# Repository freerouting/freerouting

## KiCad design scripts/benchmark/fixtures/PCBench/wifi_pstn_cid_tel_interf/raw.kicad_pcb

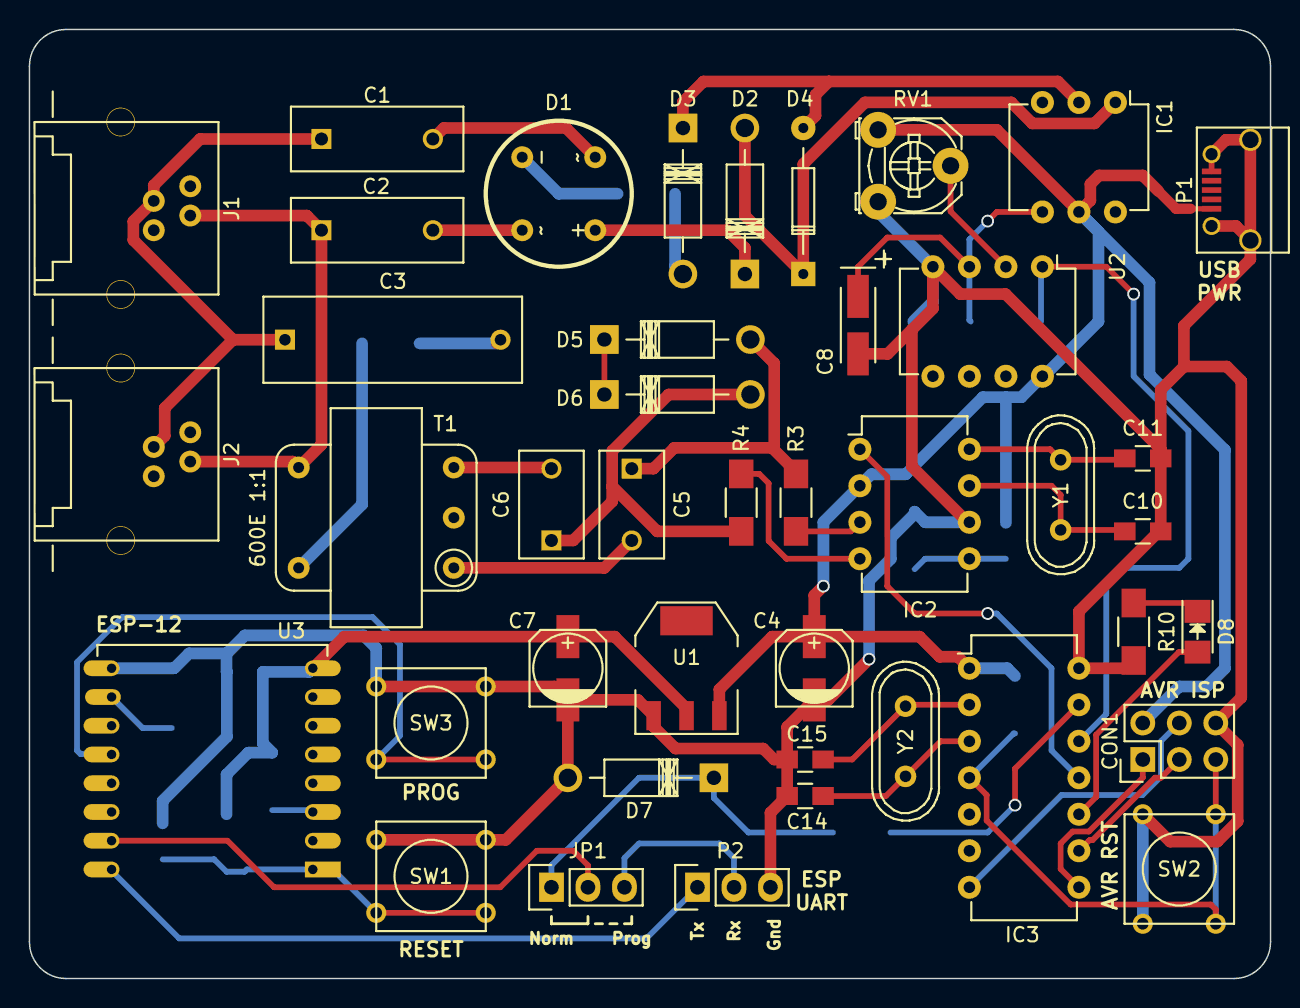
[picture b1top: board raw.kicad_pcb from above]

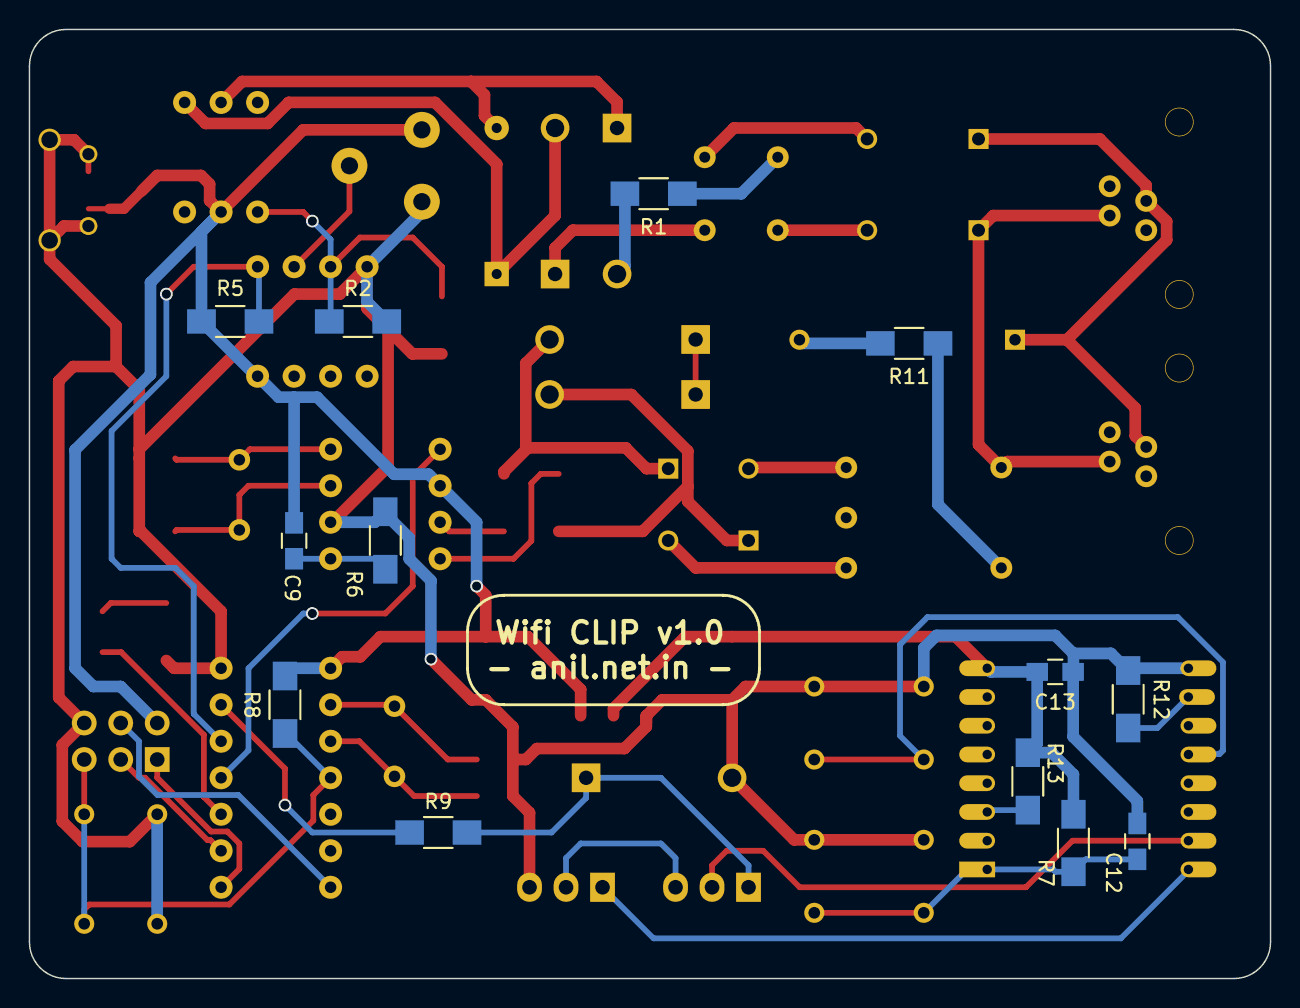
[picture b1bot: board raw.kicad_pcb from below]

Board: 2 copper layers, 86.4 x 66.0 mm, 55 parts (13 on the bottom side), 45 nets.

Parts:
C1: 33nF, 150V; C_Disc_D12_P7.75
C2: 33nF, 150v; C_Disc_D12_P7.75
C3: 100nF, 250V; C_Rect_L18_W6_P15
C4, C7: 10uF; c_elec_5x5.3
C5, C6: 47nF; C_Disc_D7.5_P5
C8: 1uF; TantalC_SizeA_EIA-3216_HandSoldering
C9, C12, C13: 0.1uF; C_0805_HandSoldering
C10, C11, C14, C15: 22pF; C_0805_HandSoldering
CON1: AVR-ISP-6; Pin_Header_Straight_2x03
D1: W10M; WOM_BRIDGE
D2, D3: ZENER 8.2V; Diode_DO-41_SOD81_Horizontal_RM10
D4: 1N4148; Diode_DO-35_SOD27_Horizontal_RM10
D5, D6: ZENER 3.3V; Diode_DO-41_SOD81_Horizontal_RM10
D7: 3.3v; Diode_DO-41_SOD81_Horizontal_RM10
D8: LED; LED-1206
IC1: 4N35; DIP-6_W7.62mm
IC2: HT9032D; DIP-8_W7.62mm
IC3: ATTINY84-P; DIP-14_W7.62mm
J1, J2: RJ11_PTH_STAGGER; RJ11_PTH_6P4C_STAG
JP1: RX sel.; Pin_Header_Straight_1x03
P1: USB_OTG; USB_Micro-B
P2: ESP_UART; Pin_Header_Straight_1x03
R1, R6: 100K; R_1206_HandSoldering
R2, R3, R4: 220K; R_1206_HandSoldering
R5: 10K; R_1206_HandSoldering
R7, R8: 4.7K; R_1206_HandSoldering
R9: 1k; R_1206_HandSoldering
R10, R11, R12, R13: 1K; R_1206_HandSoldering
RV1: 10K; Potentiometer_Triwood_RM-065
SW1: ESP_REST; SW_PUSH_SMALL
SW2: AVR_REST; SW_PUSH_SMALL
SW3: PROG; SW_PUSH_SMALL
T1: 600E 1:1; TRANSFO-AUDIO-EL14
U1: LD1117S33TR; SOT-223
U2: LM393; DIP-8_W7.62mm
U3: ESP-12
Y1: 3.579545Mhz; Crystal_HC49-U_Vertical
Y2: 8 Mhz; Crystal_HC49-U_Vertical

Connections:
+3V3: C7.1, C13.2, R7.1, R13.1, U1.2, U3.8
+5V: C4.1, C9.1, CON1.2, IC1.5, IC2.2, IC3.1, P1.1, R5.1, R8.2, RV1.1, U1.3, U2.8
AVR_MISO: CON1.1, IC3.8
AVR_MOSI: CON1.4, IC3.7
AVR_REST: CON1.5, IC3.4, R8.1, SW2.2
AVR_SCL: CON1.3, IC3.9
CLIP: IC2.1, IC3.11
GND: C4.2, C7.2, C8.2, C10.2, C11.2, C12.2, C13.1, C14.2, C15.2, CON1.6, D7.2, IC2.6, IC3.14, P1.5, P1.6, P2.3, R2.2, R6.2, R10.2, R12.1, RV1.3, SW1.1, SW2.1, SW3.1, U1.1, U2.4, U3.9
NUMOUT: IC3.13, R9.1
unnamed: C1.2, D1.4
unnamed: C2.2, D1.2
unnamed: C3.2, R11.2
unnamed: C5.1, D5.2, R3.1
unnamed: C5.2, T1.1
unnamed: C6.1, D6.2, R4.1
unnamed: C6.2, T1.3
unnamed: C8.1, IC1.4, R2.1, U2.3
unnamed: C9.2, IC2.5, R6.1
unnamed: C10.1, IC2.7, Y1.1
unnamed: C11.1, IC2.8, Y1.2
unnamed: C12.1, R7.2, SW1.2, U3.1
unnamed: C14.1, IC3.3, Y2.1
unnamed: C15.1, IC3.2, Y2.2
unnamed: D1.1, D2.1
unnamed: D1.3, R1.1
unnamed: D2.2, D4.1, IC1.1
unnamed: D3.1, D4.2, IC1.2
unnamed: D3.2, R1.2
unnamed: D5.1, D6.1
unnamed: D7.1, JP1.1, R9.2
unnamed: D8.1, R10.1
unnamed: D8.2, IC3.10
unnamed: IC2.3, R3.2
unnamed: IC2.4, R4.2
unnamed: JP1.2, U3.15
unnamed: JP1.3, P2.2
unnamed: P2.1, U3.16
unnamed: R11.1, T1.5
unnamed: R12.2, U3.10
unnamed: R13.2, U3.3
unnamed: RV1.2, U2.2
unnamed: SW3.2, U3.12
RING: IC3.12, R5.2, U2.1
TEL1: C1.1, C3.1, J1.2, J2.2
TEL2: C2.1, J1.3, J2.3, T1.4

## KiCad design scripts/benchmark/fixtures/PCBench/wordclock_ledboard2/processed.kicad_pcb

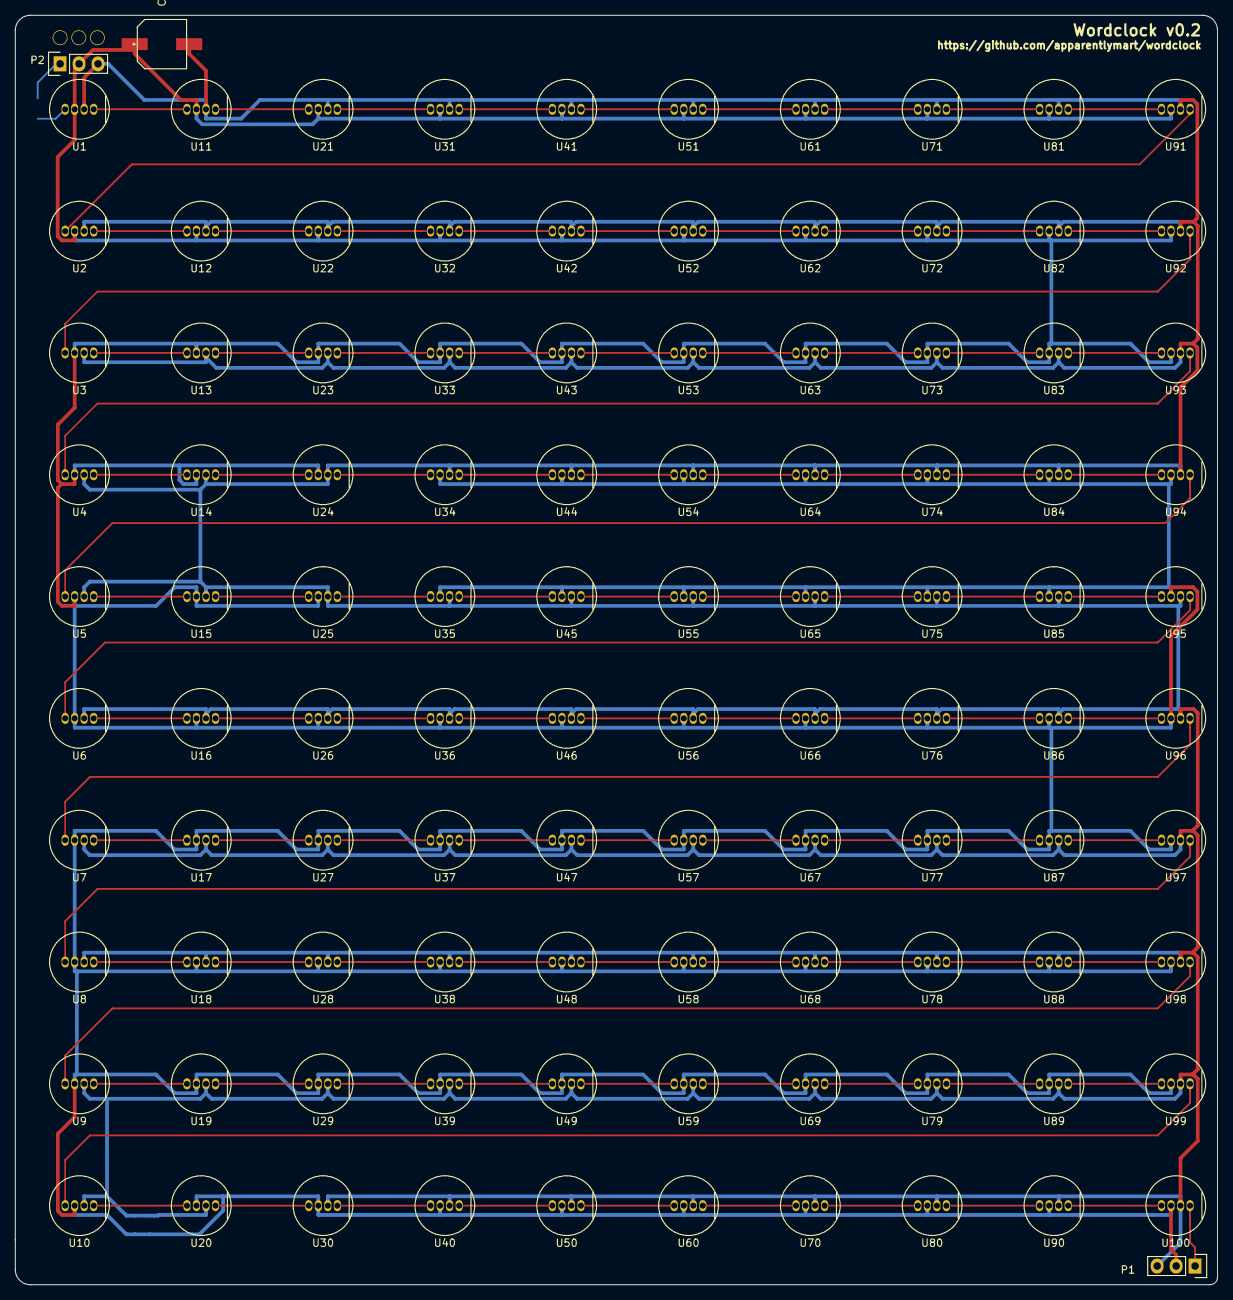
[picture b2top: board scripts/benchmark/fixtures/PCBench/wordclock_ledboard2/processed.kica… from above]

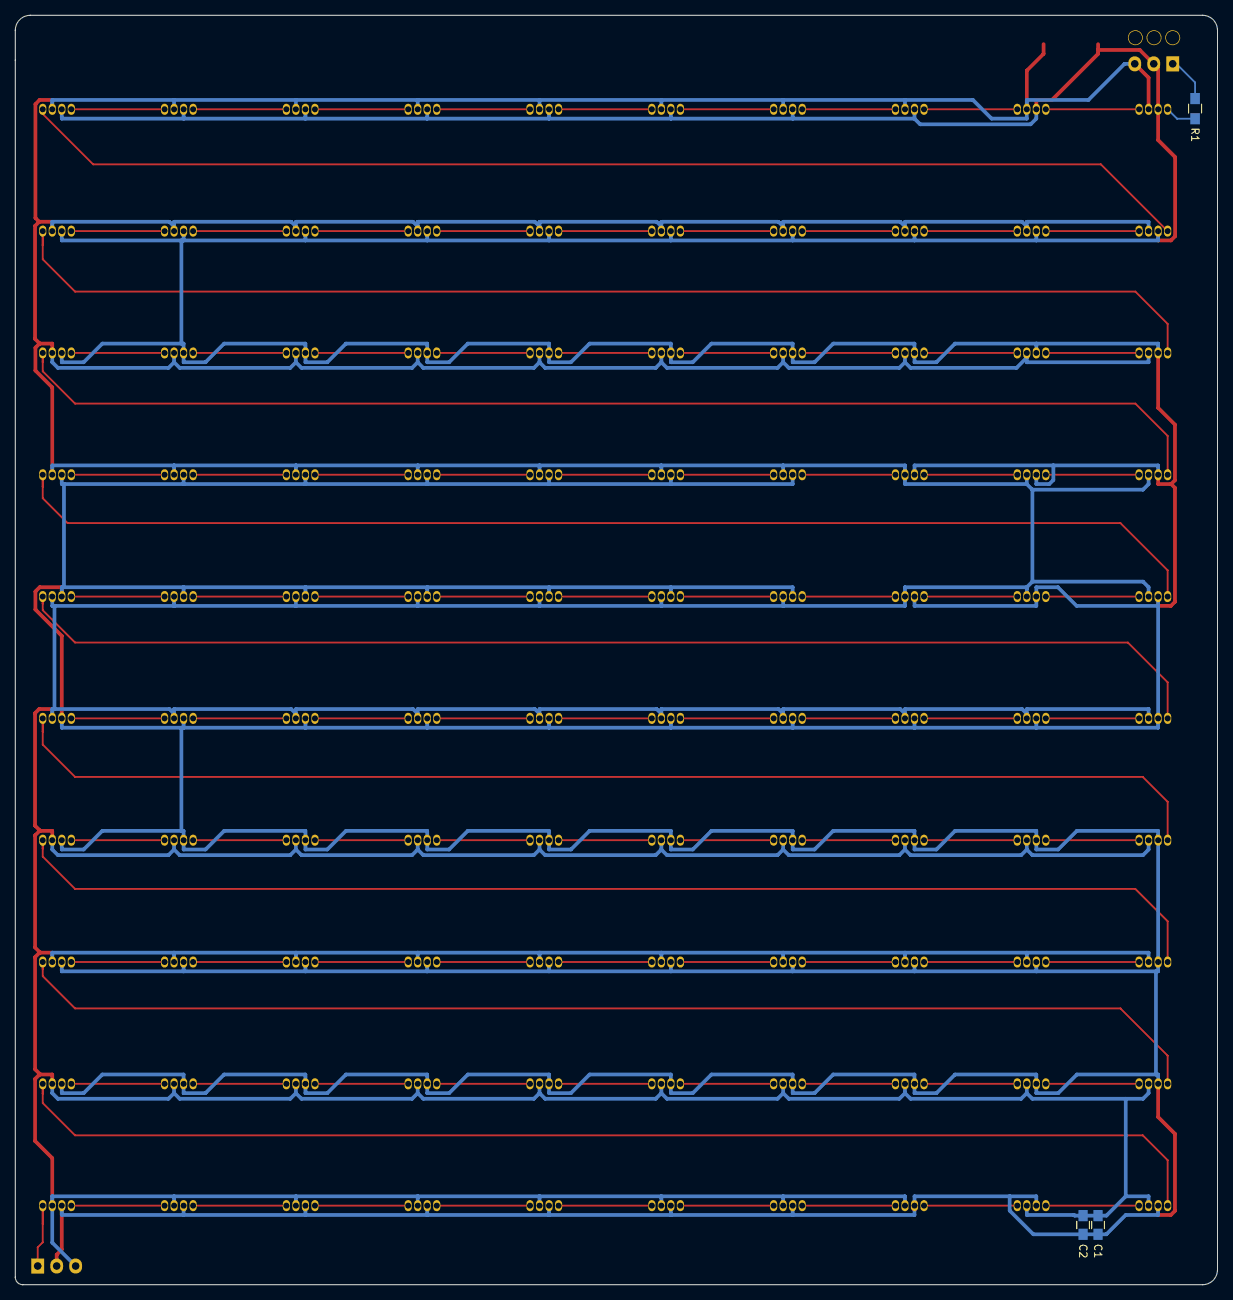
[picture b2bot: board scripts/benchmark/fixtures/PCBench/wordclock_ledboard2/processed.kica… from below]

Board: 2 copper layers, 161.0 x 170.0 mm, 106 parts (3 on the bottom side), 104 nets.

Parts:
C1, C2: 0.1u; C_0805_HandSoldering
C3: CP; CPOL_SMD_6.3mm
P1, P2: CONN_01X03; Pin_Header_Straight_1x03
R1: 300; R_0805_HandSoldering
U1, U2, U3, U4, U5, U6, U7, U8, U9, U10, U11, U12, U13, U14, U15, U16, U17, U18, U19, U20, U21, U22, U23, U24, U25, U26, U27, U28, U29, U30, U31, U32, U33, U34, U35, U36, U37, U38, U39, U40, U41, U42, U43, U44, U45, U46, U47, U48, U49, U50, U51, U52, U53, U54, U55, U56, U57, U58, U59, U60, U61, U62, U63, U64, U65, U66, U67, U68, U69, U70, U71, U72, U73, U74, U75, U76, U77, U78, U79, U80, U81, U82, U83, U84, U85, U86, U87, U88, U89, U90, U91, U92, U93, U94, U95, U96, U97, U98, U99, U100: NEOPIXEL; NEOPIXEL_8MM

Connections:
+5V: C1.1, C2.1, C3.1, P1.2, P2.2, U1.2, U2.2, U3.2, U4.2, U5.2, U6.2, U7.2, U8.2, U9.2, U10.2, U11.2, U12.2, U13.2, U14.2, U15.2, U16.2, U17.2, U18.2, U19.2, U20.2, U21.2, U22.2, U23.2, U24.2, U25.2, U26.2, U27.2, U28.2, U29.2, U30.2, U31.2, U32.2, U33.2, U34.2, U35.2, U36.2, U37.2, U38.2, U39.2, U40.2, U41.2, U42.2, U43.2, U44.2, U45.2, U46.2, U47.2, U48.2, U49.2, U50.2, U51.2, U52.2, U53.2, U54.2, U55.2, U56.2, U57.2, U58.2, U59.2, U60.2, U61.2, U62.2, U63.2, U64.2, U65.2, U66.2, U67.2, U68.2, U69.2, U70.2, U71.2, U72.2, U73.2, U74.2, U75.2, U76.2, U77.2, U78.2, U79.2, U80.2, U81.2, U82.2, U83.2, U84.2, U85.2, U86.2, U87.2, U88.2, U89.2, U90.2, U91.2, U92.2, U93.2, U94.2, U95.2, U96.2, U97.2, U98.2, U99.2, U100.2
DIN: P2.1, R1.2
DOUT: P1.1, U100.4
GND: C1.2, C2.2, C3.2, P1.3, P2.3, U1.3, U2.3, U3.3, U4.3, U5.3, U6.3, U7.3, U8.3, U9.3, U10.3, U11.3, U12.3, U13.3, U14.3, U15.3, U16.3, U17.3, U18.3, U19.3, U20.3, U21.3, U22.3, U23.3, U24.3, U25.3, U26.3, U27.3, U28.3, U29.3, U30.3, U31.3, U32.3, U33.3, U34.3, U35.3, U36.3, U37.3, U38.3, U39.3, U40.3, U41.3, U42.3, U43.3, U44.3, U45.3, U46.3, U47.3, U48.3, U49.3, U50.3, U51.3, U52.3, U53.3, U54.3, U55.3, U56.3, U57.3, U58.3, U59.3, U60.3, U61.3, U62.3, U63.3, U64.3, U65.3, U66.3, U67.3, U68.3, U69.3, U70.3, U71.3, U72.3, U73.3, U74.3, U75.3, U76.3, U77.3, U78.3, U79.3, U80.3, U81.3, U82.3, U83.3, U84.3, U85.3, U86.3, U87.3, U88.3, U89.3, U90.3, U91.3, U92.3, U93.3, U94.3, U95.3, U96.3, U97.3, U98.3, U99.3, U100.3
unnamed: R1.1, U1.1
unnamed: U1.4, U11.1
unnamed: U2.1, U91.4
unnamed: U3.1, U92.4
unnamed: U4.1, U93.4
unnamed: U5.1, U94.4
unnamed: U6.1, U95.4
unnamed: U7.1, U96.4
unnamed: U8.1, U97.4
unnamed: U9.1, U98.4
unnamed: U10.1, U99.4
unnamed: U10.4, U20.1
unnamed: U11.4, U21.1
unnamed: U2.4, U12.1
unnamed: U12.4, U22.1
unnamed: U3.4, U13.1
unnamed: U13.4, U23.1
unnamed: U4.4, U14.1
unnamed: U14.4, U24.1
unnamed: U5.4, U15.1
unnamed: U15.4, U25.1
unnamed: U6.4, U16.1
unnamed: U16.4, U26.1
unnamed: U7.4, U17.1
unnamed: U17.4, U27.1
unnamed: U8.4, U18.1
unnamed: U18.4, U28.1
unnamed: U9.4, U19.1
unnamed: U19.4, U29.1
unnamed: U20.4, U30.1
unnamed: U21.4, U31.1
unnamed: U22.4, U32.1
unnamed: U23.4, U33.1
unnamed: U24.4, U34.1
unnamed: U25.4, U35.1
unnamed: U26.4, U36.1
unnamed: U27.4, U37.1
unnamed: U28.4, U38.1
unnamed: U29.4, U39.1
unnamed: U30.4, U40.1
unnamed: U31.4, U41.1
unnamed: U32.4, U42.1
unnamed: U33.4, U43.1
unnamed: U34.4, U44.1
unnamed: U35.4, U45.1
unnamed: U36.4, U46.1
unnamed: U37.4, U47.1
unnamed: U38.4, U48.1
unnamed: U39.4, U49.1
unnamed: U40.4, U50.1
unnamed: U41.4, U51.1
unnamed: U42.4, U52.1
unnamed: U43.4, U53.1
unnamed: U44.4, U54.1
unnamed: U45.4, U55.1
unnamed: U46.4, U56.1
unnamed: U47.4, U57.1
unnamed: U48.4, U58.1
unnamed: U49.4, U59.1
unnamed: U50.4, U60.1
unnamed: U51.4, U61.1
unnamed: U52.4, U62.1
unnamed: U53.4, U63.1
unnamed: U54.4, U64.1
unnamed: U55.4, U65.1
unnamed: U56.4, U66.1
unnamed: U57.4, U67.1
unnamed: U58.4, U68.1
unnamed: U59.4, U69.1
unnamed: U60.4, U70.1
unnamed: U61.4, U71.1
unnamed: U62.4, U72.1
unnamed: U63.4, U73.1
unnamed: U64.4, U74.1
unnamed: U65.4, U75.1
unnamed: U66.4, U76.1
unnamed: U67.4, U77.1
unnamed: U68.4, U78.1
unnamed: U69.4, U79.1
unnamed: U70.4, U80.1
unnamed: U71.4, U81.1
unnamed: U72.4, U82.1
unnamed: U73.4, U83.1
unnamed: U74.4, U84.1
unnamed: U75.4, U85.1
unnamed: U76.4, U86.1
unnamed: U77.4, U87.1
unnamed: U78.4, U88.1
unnamed: U79.4, U89.1
unnamed: U80.4, U90.1
unnamed: U81.4, U91.1
unnamed: U82.4, U92.1
unnamed: U83.4, U93.1
unnamed: U84.4, U94.1
unnamed: U85.4, U95.1
unnamed: U86.4, U96.1
unnamed: U87.4, U97.1
unnamed: U88.4, U98.1
unnamed: U89.4, U99.1
unnamed: U90.4, U100.1

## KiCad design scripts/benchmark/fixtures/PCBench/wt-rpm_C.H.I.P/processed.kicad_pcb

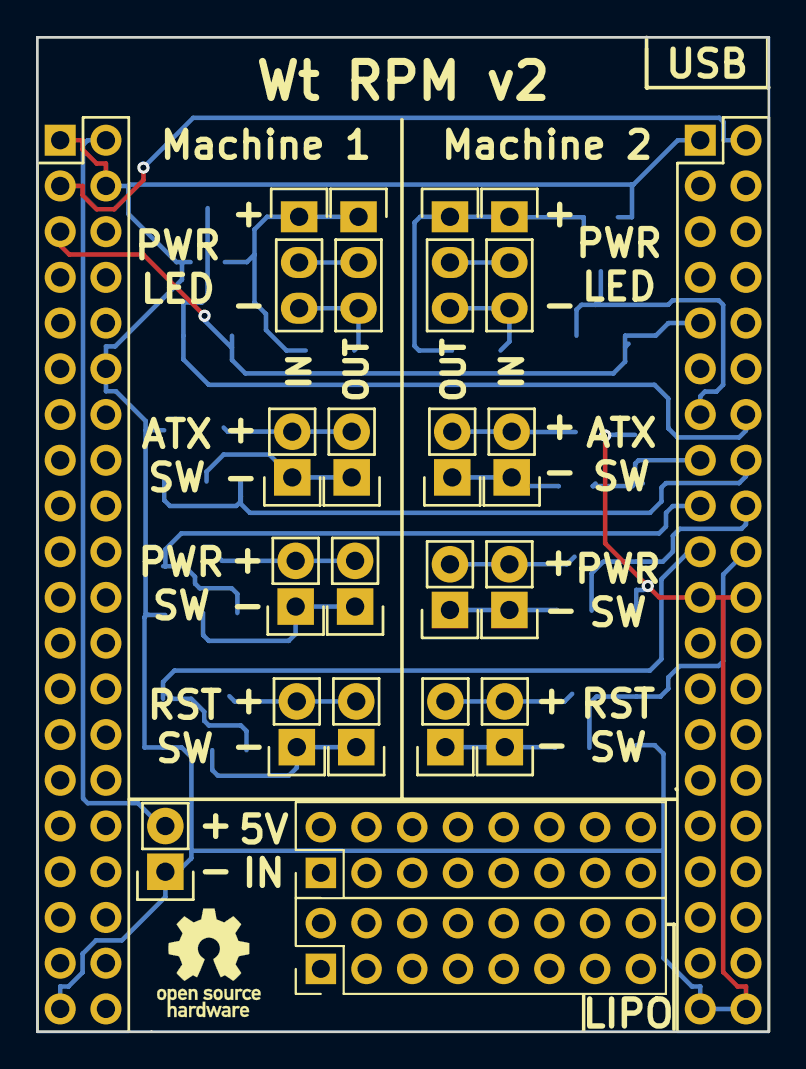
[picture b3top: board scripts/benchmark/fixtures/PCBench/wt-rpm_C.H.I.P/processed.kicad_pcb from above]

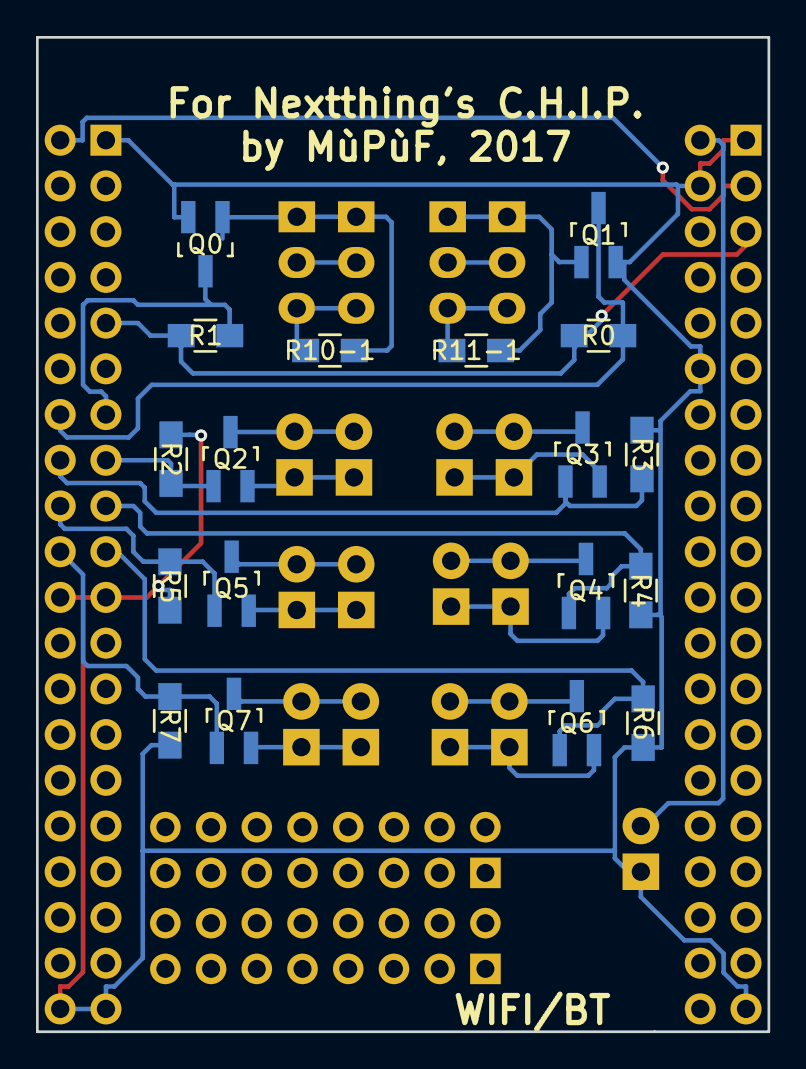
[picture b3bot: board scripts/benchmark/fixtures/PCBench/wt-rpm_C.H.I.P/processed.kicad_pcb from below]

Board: 2 copper layers, 40.6 x 55.2 mm, 39 parts (18 on the bottom side), 30 nets.

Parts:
J13, J14: DIP-HEADER-2x20; DIP_Header_2x20
P0, P0-1, P1-0, P1-1: CONN_01X03; Pin_Header_Straight_1x03
P2-0, P2-1, P3-0, P3-1, P4-0, P4-1, P5-0, P5-1, P6-0, P6-1, P7-0, P7-1, P7-CHG1: CONN_01X02; Pin_Header_Straight_1x02
Q0, Q1: SOT-23_Handsoldering
Q2, Q3, Q4, Q5, Q6, Q7: MOSFET-NCHANNELSMD; SOT-23_Handsoldering
R0, R1, R2, R3, R4, R5, R6, R7, R10-1, R11-1: 10k; R_0805_HandSoldering
SCRATCH0, SCRATCH1: Pin_Header_Straight_2x08_Pitch2.54mm

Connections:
+3.3V: J13.5, J14.9, R0.2, R1.1
+5V: J13.3, J14.2
/XIO-P0: J14.13, Q0.3, R1.2
/XIO-P1: J14.14, Q1.3, R0.1
/XIO-P2: J14.15, Q2.1, R2.1
/XIO-P3: J14.16, Q3.1, R3.1
/XIO-P4: J14.17, Q4.1, R4.1
/XIO-P5: J14.18, Q5.1, R5.1
/XIO-P6: J14.19, Q6.1, R6.1
/XIO-P7: J14.20, Q7.1, R7.1
GND: J13.1, J13.4, J13.12, J13.39, J14.1, J14.21, J14.22, J14.39, J14.40, P7-CHG1.1, Q0.2, Q1.2, R2.2, R3.2, R4.2, R5.2, R6.2, R7.2
unnamed: P0.1, P0-1.1, Q0.1, R10-1.2
unnamed: P0.2, P0-1.2
unnamed: P0.3, P0-1.3, R10-1.1
unnamed: P1-0.1, P1-1.1, Q1.1, R11-1.2
unnamed: P1-0.2, P1-1.2
unnamed: P1-0.3, P1-1.3, R11-1.1
unnamed: P2-0.1, P2-1.1, Q2.2
unnamed: P2-0.2, P2-1.2, Q2.3
unnamed: P3-0.1, P3-1.1, Q3.2
unnamed: P3-0.2, P3-1.2, Q3.3
unnamed: P4-0.1, P4-1.1, Q4.2
unnamed: P4-0.2, P4-1.2, Q4.3
unnamed: P5-0.1, P5-1.1, Q5.2
unnamed: P5-0.2, P5-1.2, Q5.3
unnamed: P6-0.1, P6-1.1, Q6.2
unnamed: P6-0.2, P6-1.2, Q6.3
unnamed: P7-0.1, P7-1.1, Q7.2
unnamed: P7-0.2, P7-1.2, Q7.3
VCHG: J13.2, P7-CHG1.2

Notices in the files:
scripts/benchmark/fixtures/PCBench/wt-rpm_C.H.I.P/processed.kicad_pcb:
Released under the CERN Open Hardware License v1.2
